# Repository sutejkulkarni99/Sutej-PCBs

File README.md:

# Sutej-PCBs
PCBs designs (Accenture Umlaut)

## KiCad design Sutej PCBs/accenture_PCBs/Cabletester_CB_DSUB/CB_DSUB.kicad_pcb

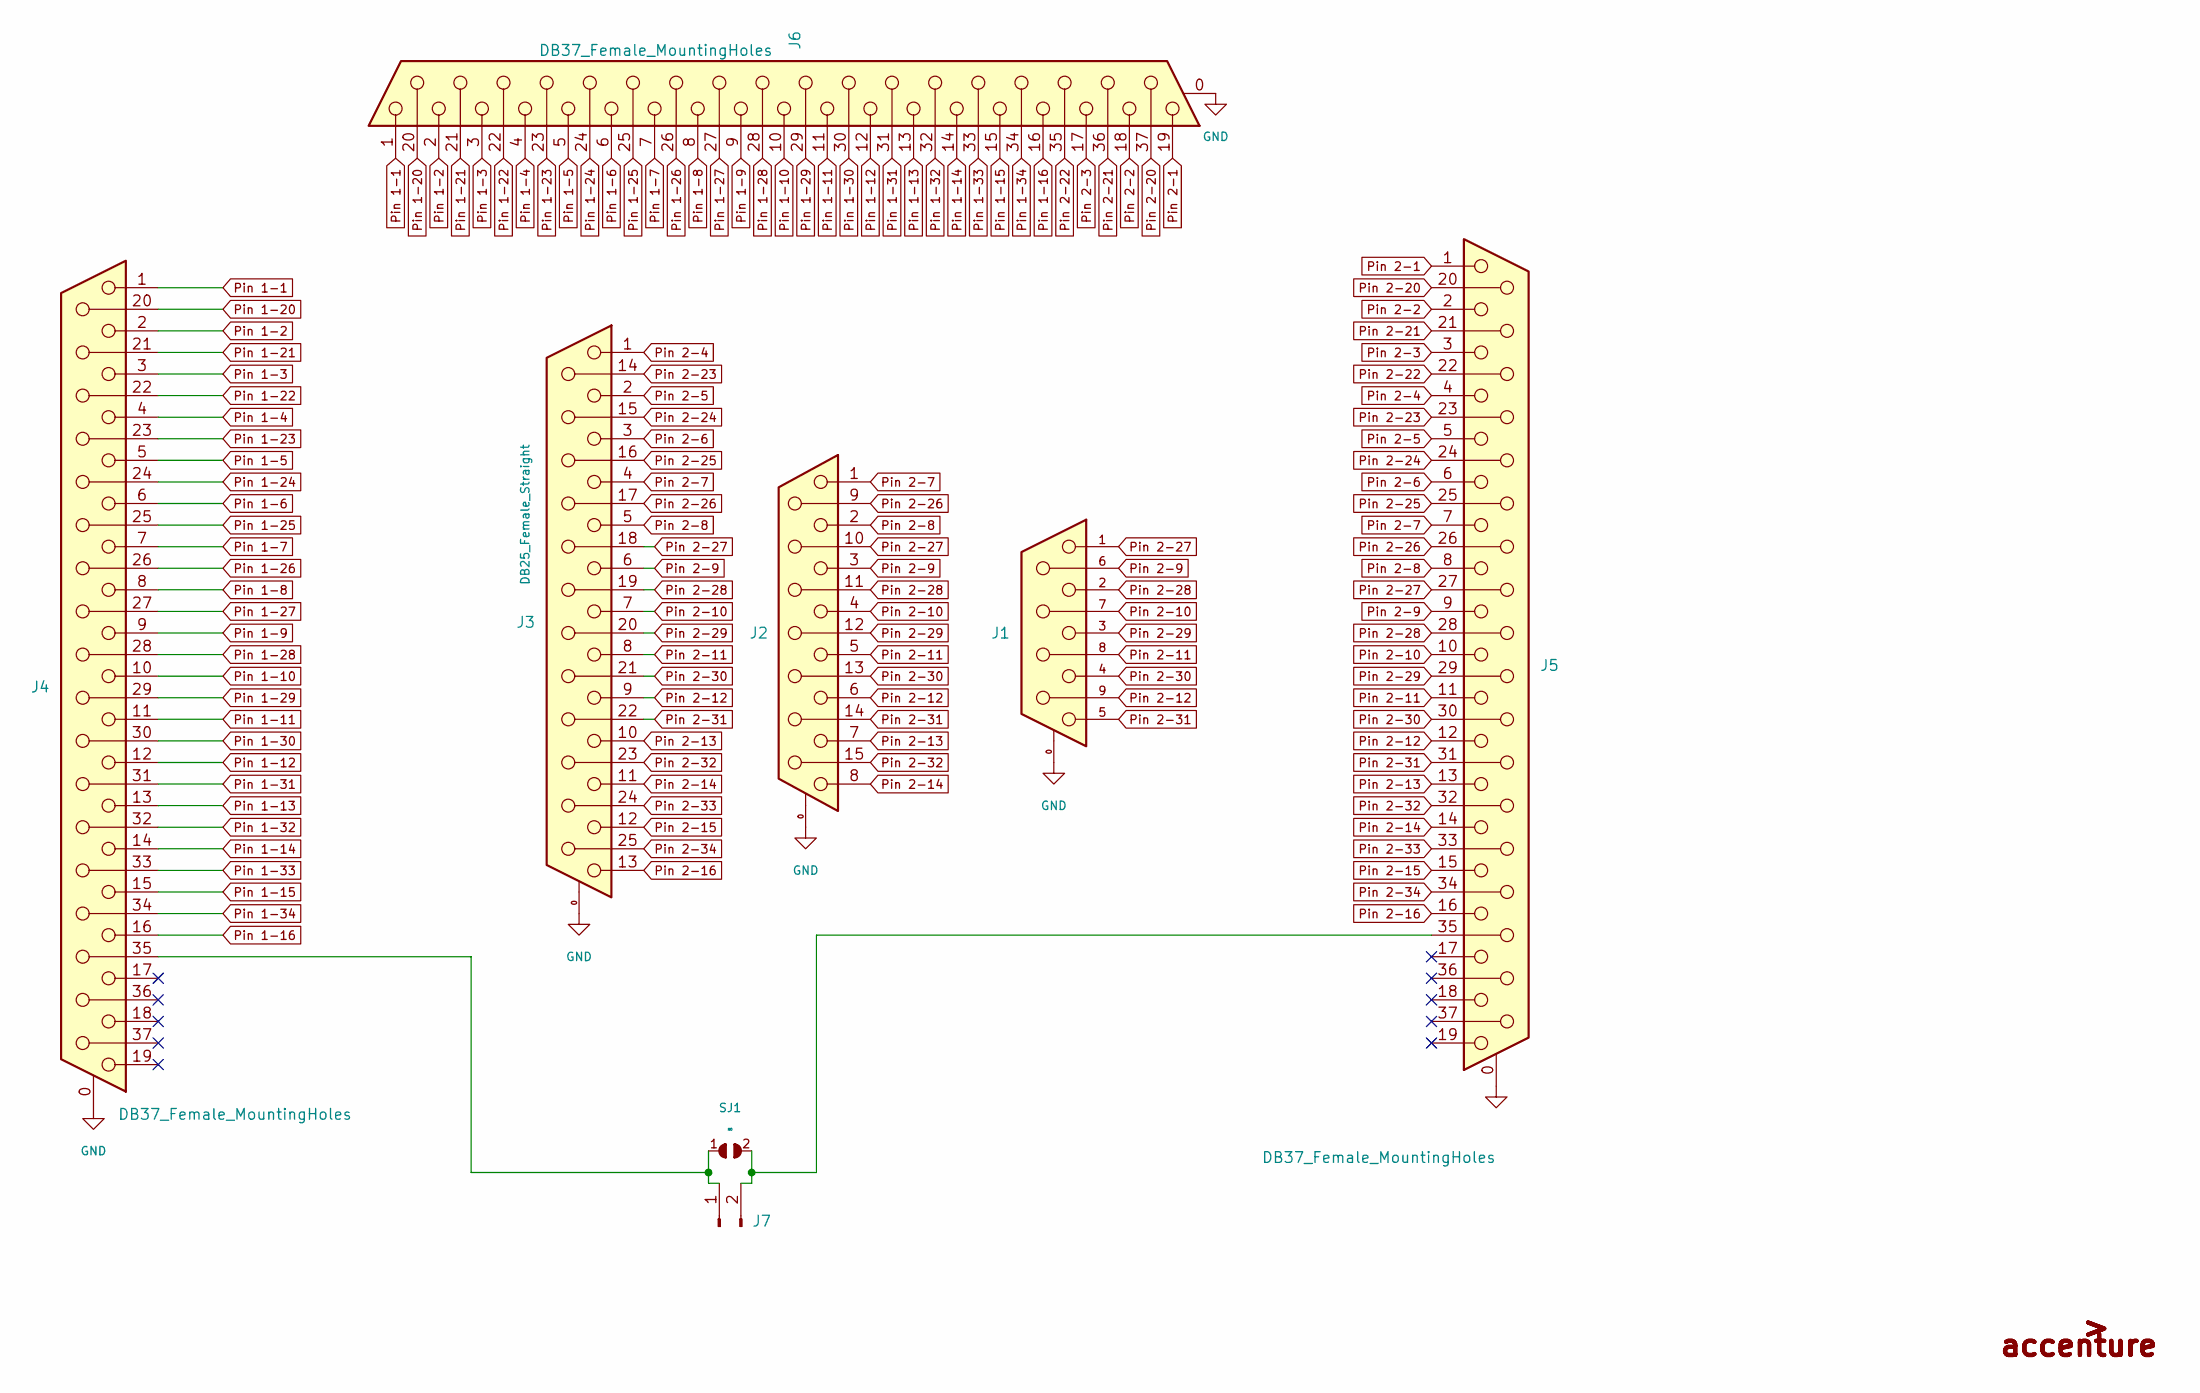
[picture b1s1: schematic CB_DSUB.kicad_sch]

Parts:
J1: DB9_Female_Straight; DSUB-9_Female_Vertical_P2.77x2.84mm_MountingHoles_FCC; Farnell 2401252
J2: DB15_Female_Straight; DSUB-15_Female_Vertical_P2.77x2.84mm_MountingHoles; Farnell 2857978
J3: DB25_Female_Straight; DSUB-25_Female_Vertical_P2.77x2.84mm-FCC; Farnell 3727279
J4, J5, J6: DB37_Female_MountingHoles; DSUB-37_Female_Vertical_P2.77x2.84mm_MountingHoles; Farnell 2401248
J7: Conn_01x02_Male; Molex_KK254_22032021_01_02x2.54mm_Straight; Farnell 9731075
Logo2, Logo3: Accenture-LOGO-13x3; Accenture-13x3
SJ1: SolderJumper-2pin; SJ

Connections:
GND: J1.0 (Shield), J2.0 (Shield), J3.0 (Shield), J4.0 (PAD), J5.0 (PAD), J6.0 (PAD)
unnamed: J4.35, J7.1, SJ1.1
unnamed: J5.35, J7.2, SJ1.2
Pin 1-1: J4.1, J6.1
Pin 1-2: J4.2, J6.2
Pin 1-3: J4.3, J6.3
Pin 1-4: J4.4, J6.4
Pin 1-5: J4.5, J6.5
Pin 1-6: J4.6, J6.6
Pin 1-7: J4.7, J6.7
Pin 1-8: J4.8, J6.8
Pin 1-9: J4.9, J6.9
Pin 1-10: J4.10, J6.10
Pin 1-11: J4.11, J6.11
Pin 1-12: J4.12, J6.12
Pin 1-13: J4.13, J6.13
Pin 1-14: J4.14, J6.14
Pin 1-15: J4.15, J6.15
Pin 1-16: J4.16, J6.16
Pin 1-20: J4.20, J6.20
Pin 1-21: J4.21, J6.21
Pin 1-22: J4.22, J6.22
Pin 1-23: J4.23, J6.23
Pin 1-24: J4.24, J6.24
Pin 1-25: J4.25, J6.25
Pin 1-26: J4.26, J6.26
Pin 1-27: J4.27, J6.27
Pin 1-28: J4.28, J6.28
Pin 1-29: J4.29, J6.29
Pin 1-30: J4.30, J6.30
Pin 1-31: J4.31, J6.31
Pin 1-32: J4.32, J6.32
Pin 1-33: J4.33, J6.33
Pin 1-34: J4.34, J6.34
Pin 2-1: J5.1, J6.19
Pin 2-2: J5.2, J6.18
Pin 2-3: J5.3, J6.17
Pin 2-4: J3.1, J5.4
Pin 2-5: J3.2, J5.5
Pin 2-6: J3.3, J5.6
Pin 2-7: J2.1, J3.4, J5.7
Pin 2-8: J2.2, J3.5, J5.8
Pin 2-9: J1.6, J2.3, J3.6, J5.9
Pin 2-10: J1.7, J2.4, J3.7, J5.10
Pin 2-11: J1.8, J2.5, J3.8, J5.11
Pin 2-12: J1.9, J2.6, J3.9, J5.12
Pin 2-13: J2.7, J3.10, J5.13
Pin 2-14: J2.8, J3.11, J5.14
Pin 2-15: J3.12, J5.15
Pin 2-16: J3.13, J5.16
Pin 2-20: J5.20, J6.37
Pin 2-21: J5.21, J6.36
Pin 2-22: J5.22, J6.35
Pin 2-23: J3.14, J5.23
Pin 2-24: J3.15, J5.24
Pin 2-25: J3.16, J5.25
Pin 2-26: J2.9, J3.17, J5.26
Pin 2-27: J1.1, J2.10, J3.18, J5.27
Pin 2-28: J1.2, J2.11 (P111), J3.19, J5.28
Pin 2-29: J1.3, J2.12, J3.20, J5.29
Pin 2-30: J1.4, J2.13, J3.21, J5.30
Pin 2-31: J1.5, J2.14, J3.22, J5.31
Pin 2-32: J2.15, J3.23, J5.32
Pin 2-33: J3.24, J5.33
Pin 2-34: J3.25, J5.34

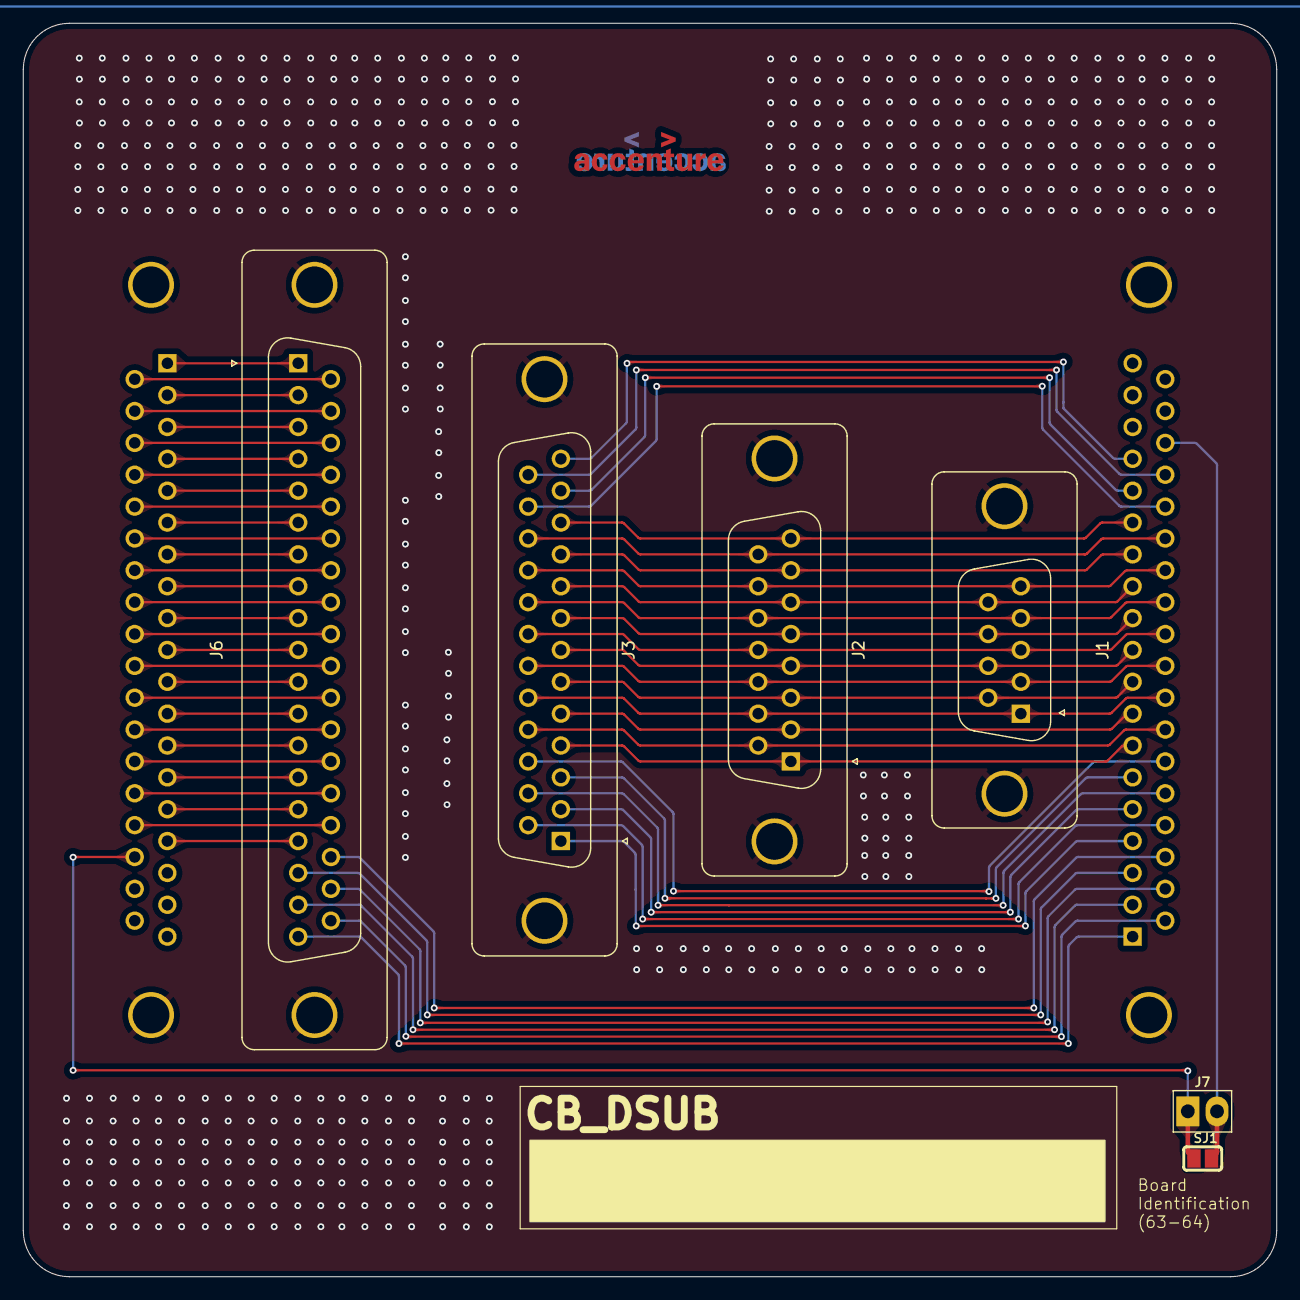
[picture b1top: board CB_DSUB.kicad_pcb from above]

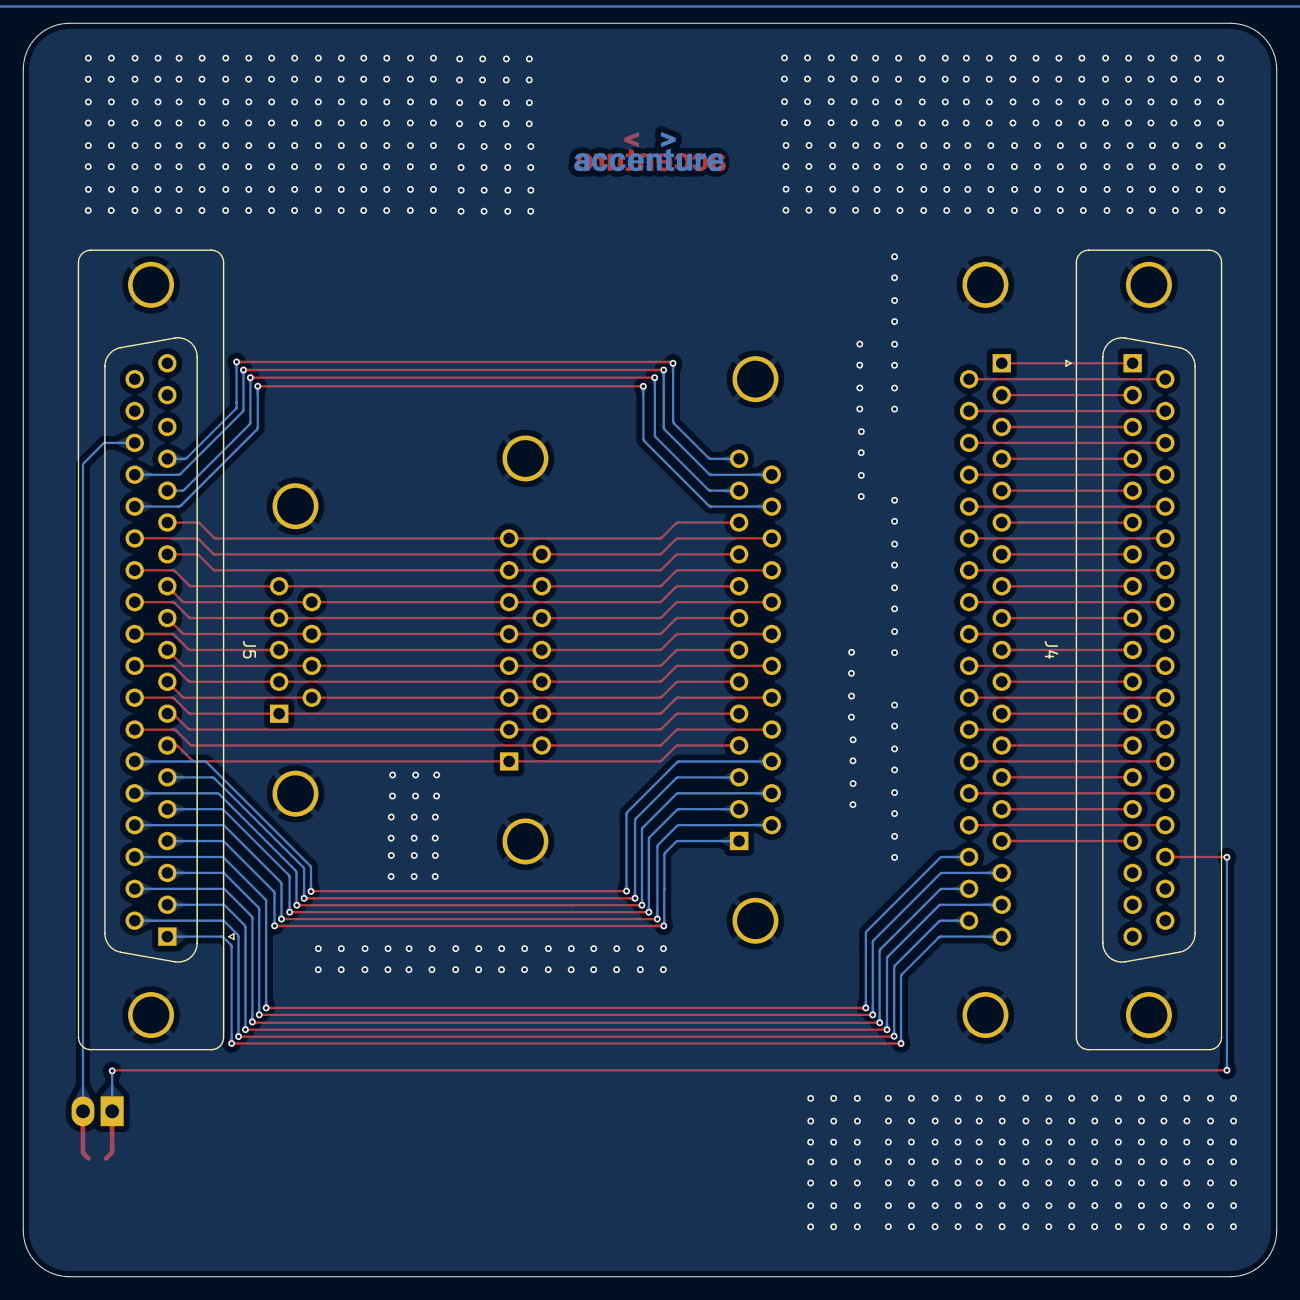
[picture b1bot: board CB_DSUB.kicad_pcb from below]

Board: 2 copper layers, 109.0 x 109.0 mm, 10 parts (3 on the bottom side), 65 nets.

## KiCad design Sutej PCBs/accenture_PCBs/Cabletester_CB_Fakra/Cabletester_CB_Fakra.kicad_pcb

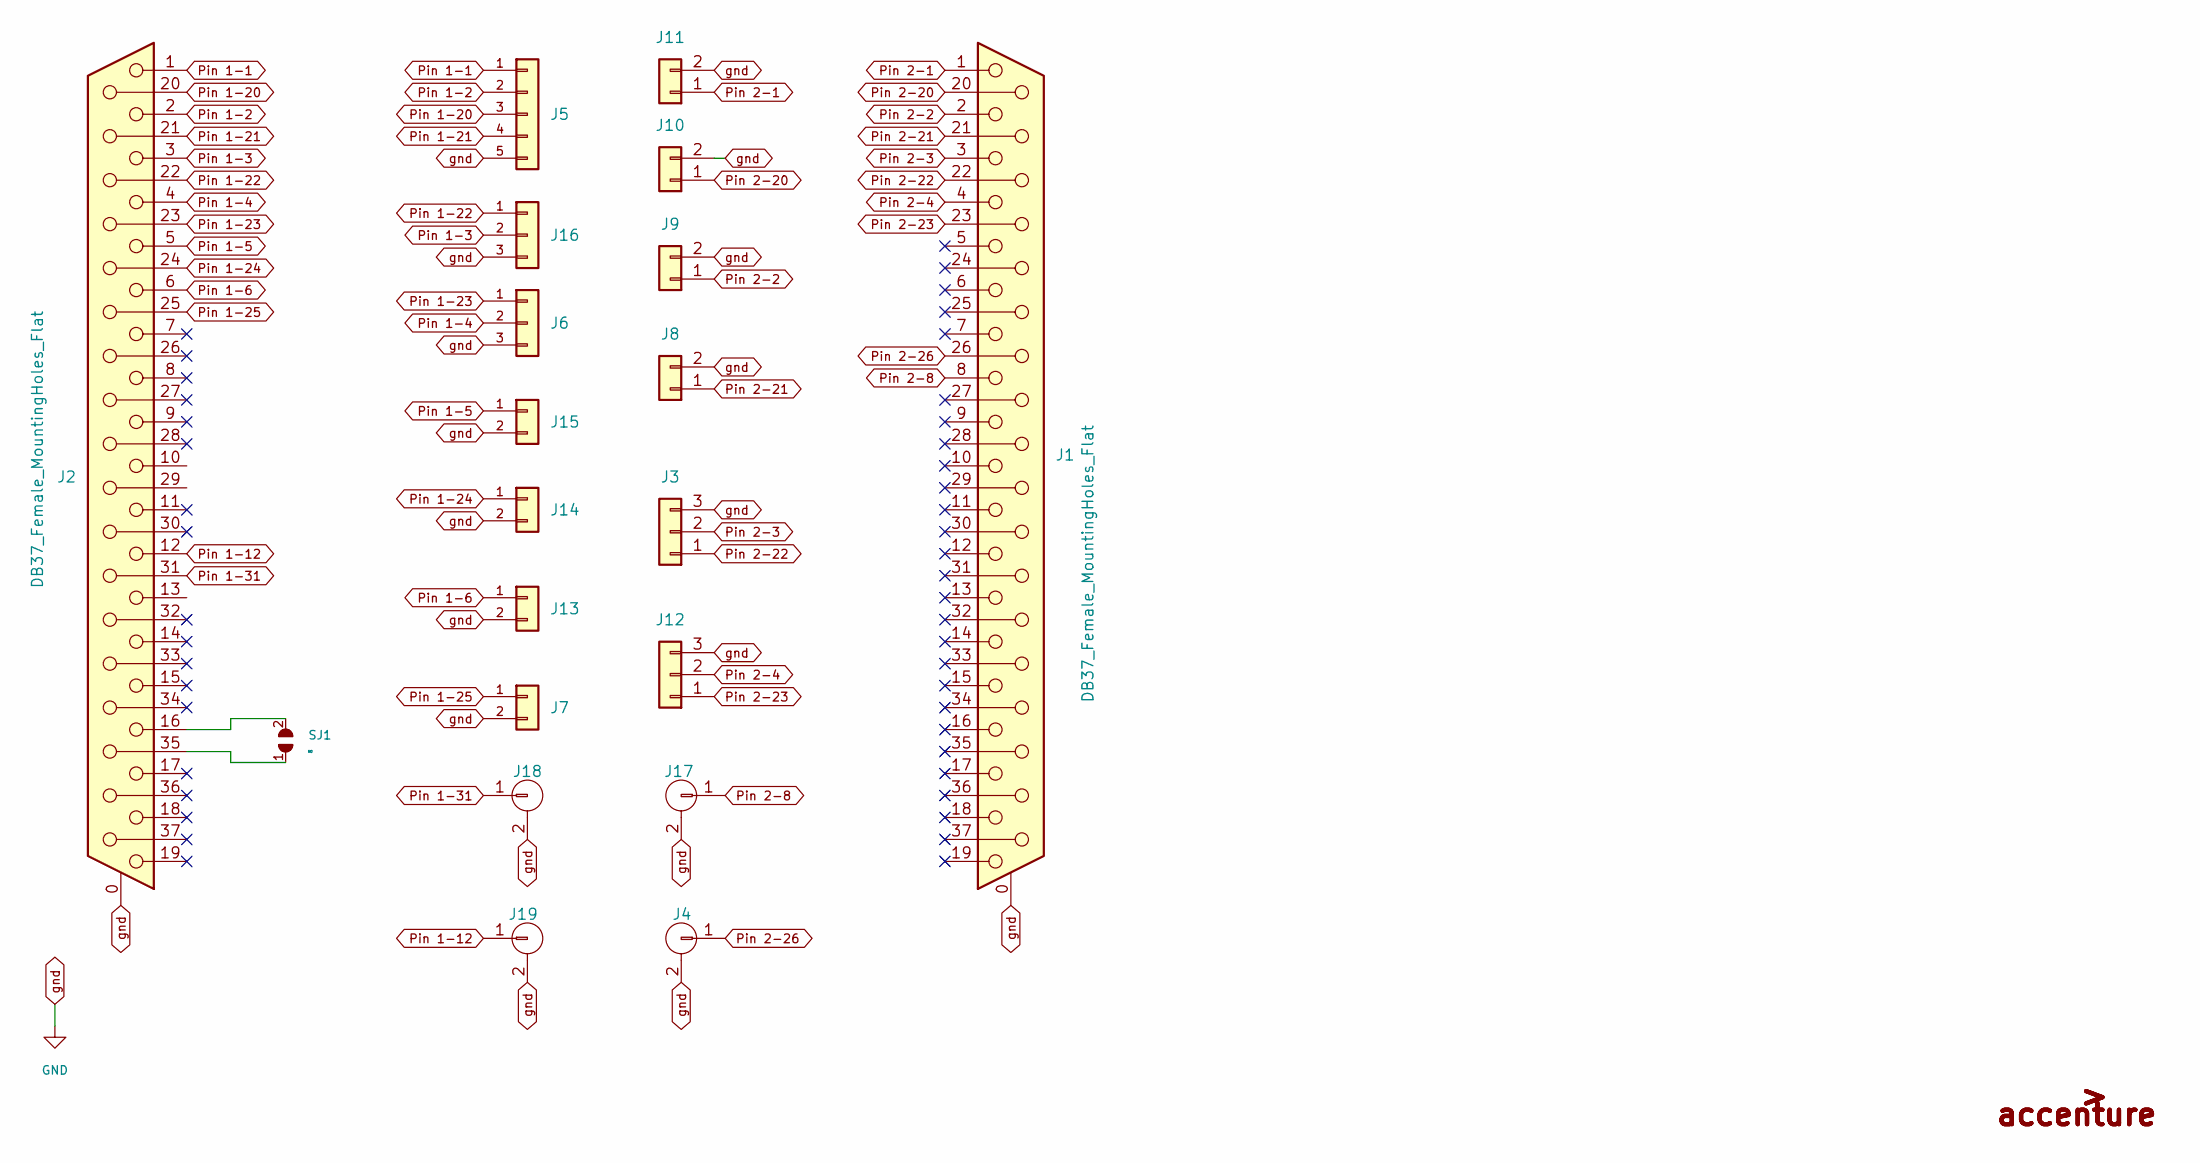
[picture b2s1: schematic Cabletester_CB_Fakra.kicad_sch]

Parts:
J1, J2: DB37_Female_MountingHoles_Flat; DSUB-37_Female_Vertical_P2.77x2.84mm_Flat_MountingHoles; Farnell 3882315
J3, J12: Rosenberger-59S2AA-400A5-G; 59S2AA-400A5-G
J4, J17, J18, J19: BNC-Female-PCB; BNC_731711900; Farnell 1909223
J5: Rosenberger-AMS29D-40MZ5-A; AMS29D-40MZ5-A
J6, J16: Rosenberger-AMS29B-40MZ5-Z; AMS29B-40MZ5-Z
J7, J13, J14, J15: Rosenberger-AMS29A-40MZ5-Z; AMS29A-40MZ5-Z
J8, J9, J10, J11: Rosenberger-59S2AQ-40MT5-C_1; 59S2AQ-40MT5-C_1
Logo1, Logo2: Accenture-LOGO-13x3; Accenture-13x3
SJ1: SolderJumper-2pin; SJ

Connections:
unnamed: J2.16, SJ1.2
unnamed: J2.35, SJ1.1
Pin 1-1: J2.1, J5.1
Pin 1-2: J2.2, J5.2
Pin 1-3: J2.3, J16.2
Pin 1-4: J2.4, J6.2
Pin 1-5: J2.5, J15.1
Pin 1-6: J2.6, J13.1
Pin 1-12: J2.12, J19.1
Pin 1-20: J2.20, J5.3 (Pin_2)
Pin 1-21: J2.21, J5.4 (Pin_2)
Pin 1-22: J2.22, J16.1
Pin 1-23: J2.23, J6.1
Pin 1-24: J2.24, J14.1
Pin 1-25: J2.25, J7.1
Pin 1-31: J2.31, J18.1
Pin 2-1: J1.1, J11.1
Pin 2-2: J1.2, J9.1
Pin 2-3: J1.3, J3.2
Pin 2-4: J1.4, J12.2
Pin 2-8: J1.8, J17.1
Pin 2-20: J1.20, J10.1
Pin 2-21: J1.21, J8.1
Pin 2-22: J1.22, J3.1
Pin 2-23: J1.23, J12.1
Pin 2-26: J1.26, J4.1
gnd: J1.0 (PAD), J2.0 (PAD), J3.3 (Pin_2), J4.2 (GND), J5.5 (Pin_2), J6.3 (Pin_2), J7.2, J8.2, J9.2, J10.2, J11.2, J12.3 (Pin_2), J13.2, J14.2, J15.2, J16.3 (Pin_2), J17.2 (GND), J18.2 (GND), J19.2 (GND)

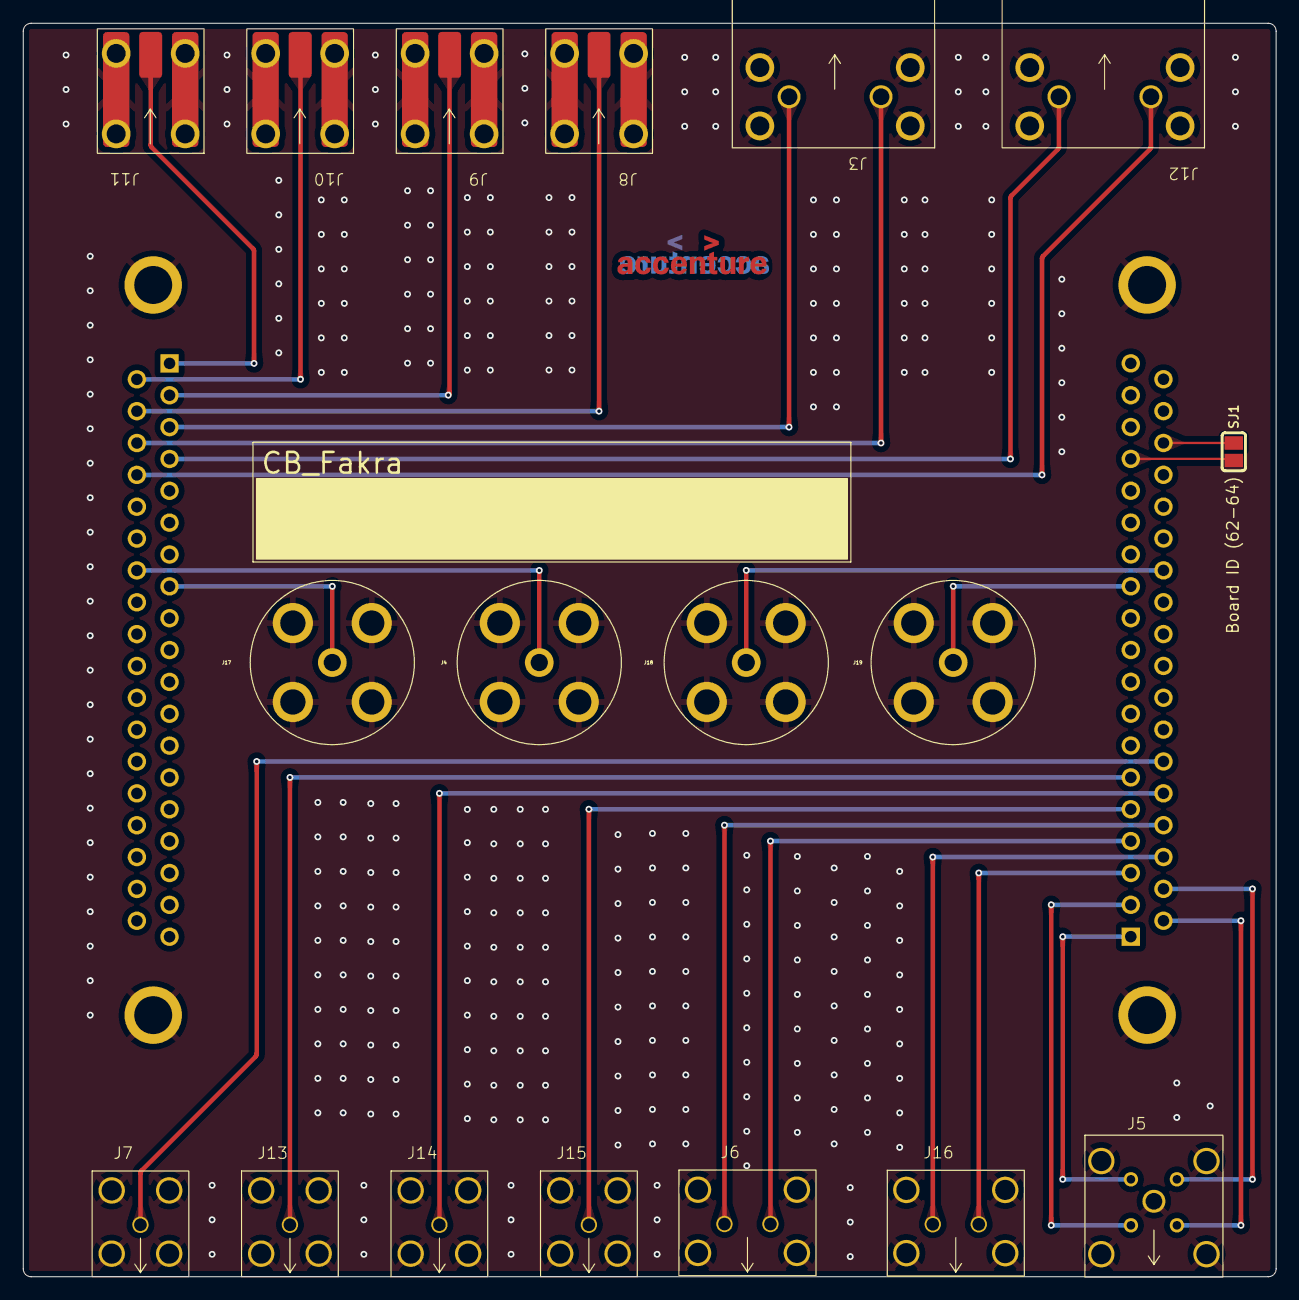
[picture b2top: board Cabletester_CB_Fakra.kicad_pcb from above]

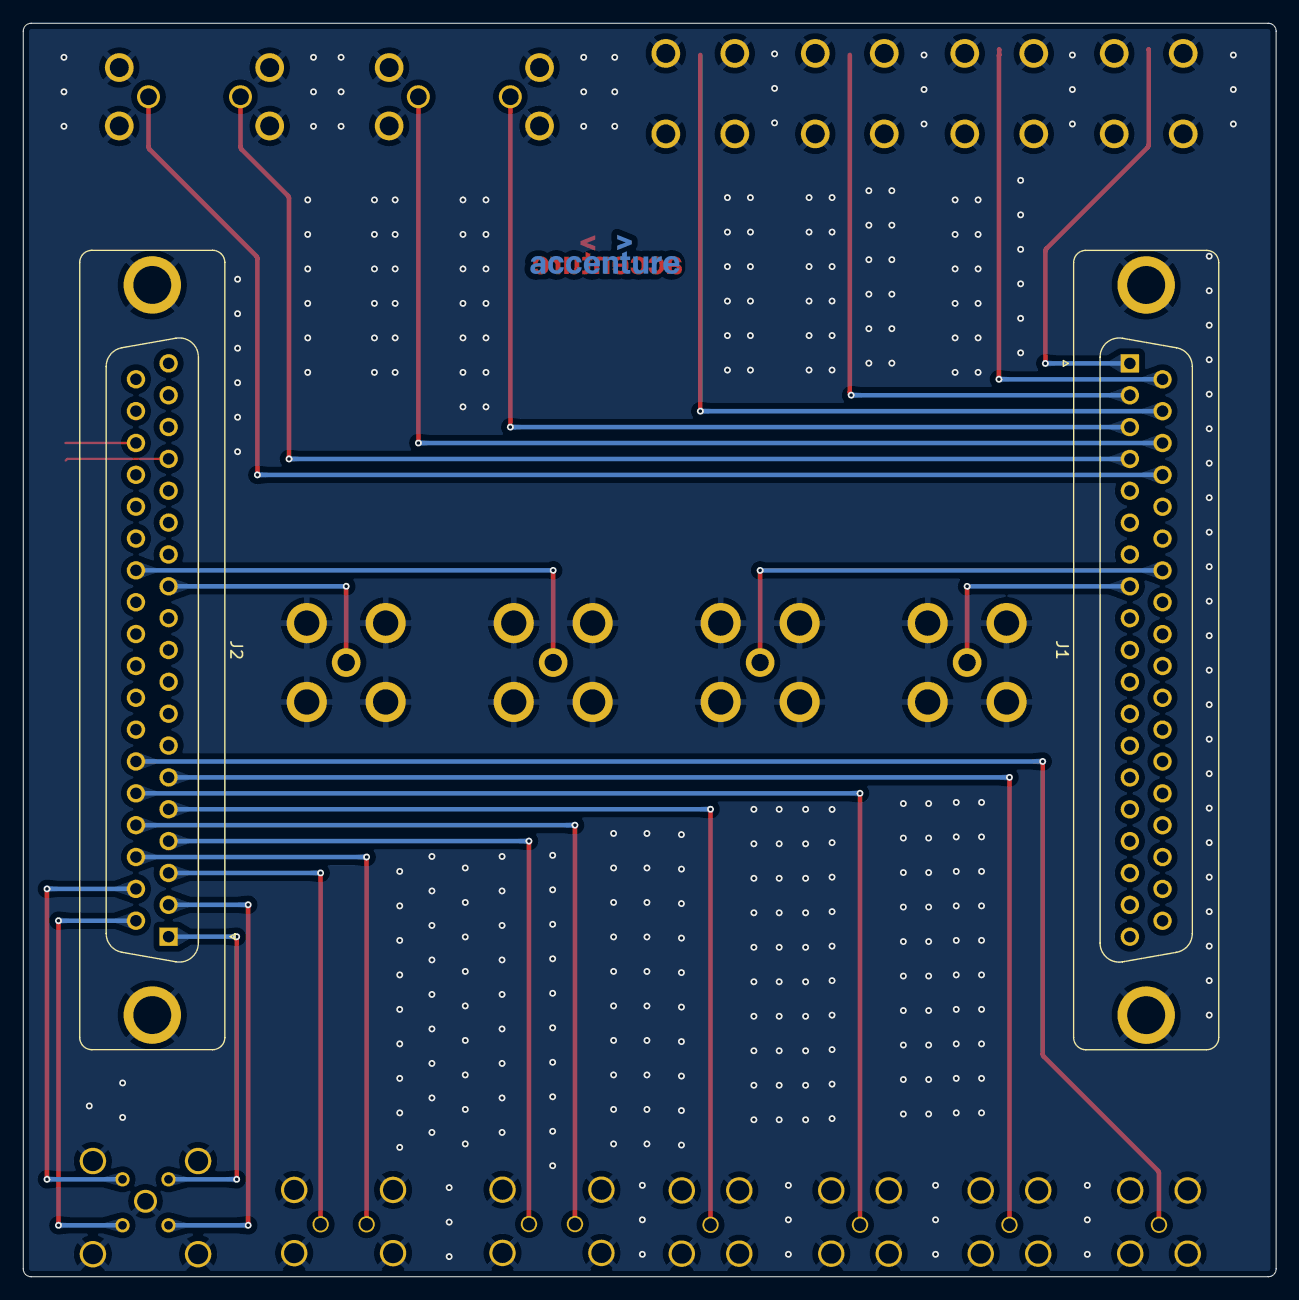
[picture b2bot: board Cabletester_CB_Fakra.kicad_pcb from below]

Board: 2 copper layers, 109.0 x 109.0 mm, 22 parts (3 on the bottom side), 27 nets.

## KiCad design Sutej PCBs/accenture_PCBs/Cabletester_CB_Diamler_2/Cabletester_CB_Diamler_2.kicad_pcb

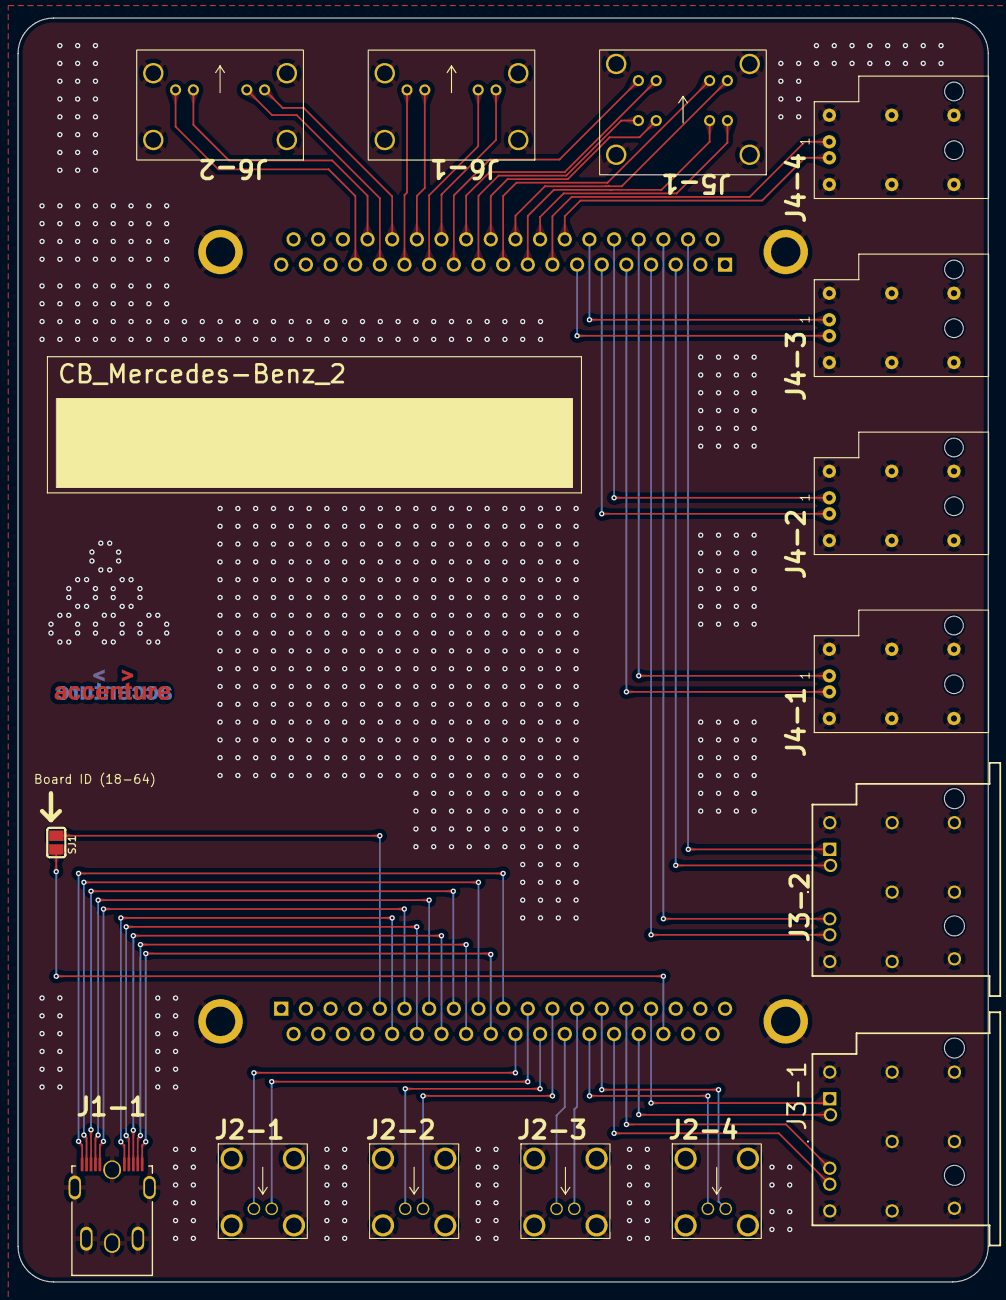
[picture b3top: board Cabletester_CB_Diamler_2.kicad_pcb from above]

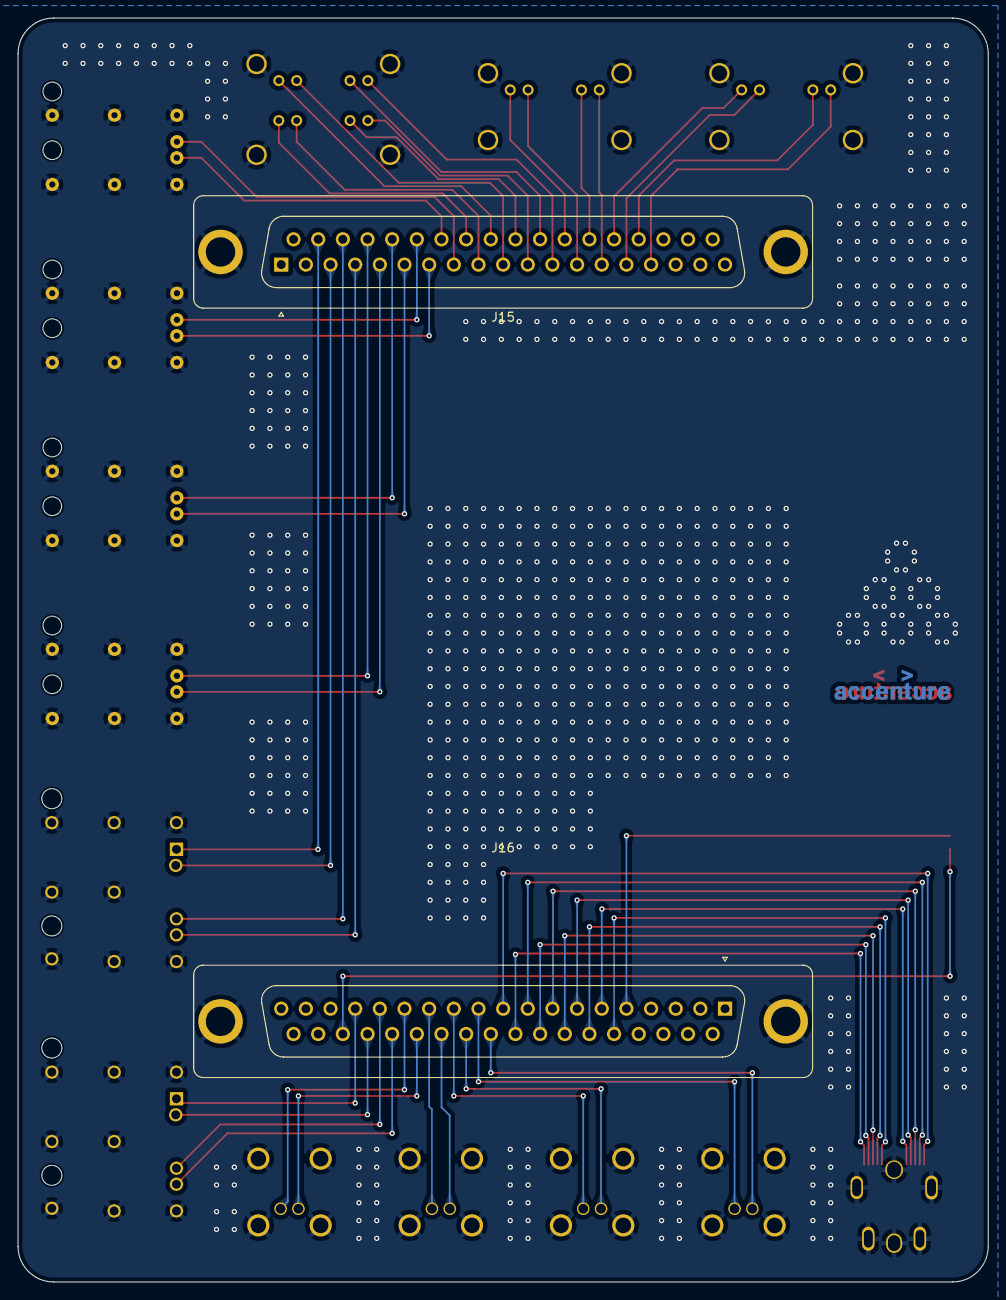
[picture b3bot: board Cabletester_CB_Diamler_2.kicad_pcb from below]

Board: 2 copper layers, 109.0 x 142.0 mm, 19 parts (3 on the bottom side), 53 nets.

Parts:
J1-1: Daimler-IX61G-A-10P; IX61G-A-10P
J2-1, J2-2, J2-3, J2-4: Rosenberger-E6S20A-40MT5-Z; E6S20A-40MT5-Z
J3-1, J3-2: TE-9-2305987-9; 9-2305987-9
J4-1, J4-2, J4-3, J4-4: Conn_01x04_1.27mm_Female; TE-c-9-2304372-9-a
J5-1: Rosenberger-E6S20D-40MT5-Z; E6S20D-40MT5-Z
J6-1, J6-2: Rosenberger-E6S20B-40MT5-Z; E6S20B-40MT5-Z
J15, J16: DB37_Female_MountingHoles_Flat; DSUB-37_Female_Vertical_P2.77x2.84mm_Flat_MountingHoles
Logo1, Logo2: Accenture-LOGO-13x3; Accenture-13x3
SJ1: SolderJumper-2pin; SJ

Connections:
GND: J1-1.11 (GND), J2-1.3 (Pin_2), J2-2.3 (Pin_2), J2-3.3 (Pin_2), J2-4.3 (Pin_2), J3-1.5, J3-2.5, J4-1.3, J4-1.4, J4-2.3, J4-2.4, J4-3.3, J4-3.4, J4-4.3, J4-4.4, J5-1.5 (Pin_2), J6-1.5 (Pin_2), J6-2.5 (Pin_2), J15.0 (PAD), J16.0 (PAD)
unnamed: J16.5, SJ1.1
unnamed: J16.35, SJ1.2
Pin 1-3: J3-2.2, J15.3
Pin 1-4: J3-2.4, J15.4
Pin 1-5: J4-1.2, J15.5
Pin 1-6: J4-2.2, J15.6
Pin 1-7: J4-3.2, J15.7
Pin 1-8: J4-4.1, J15.8
Pin 1-9: J5-1.1-2 (Pair1), J15.9
Pin 1-10: J5-1.4-1 (Pair4), J15.10
Pin 1-11: J5-1.2-2 (Pair2), J15.11
Pin 1-12: J5-1.3-1 (Pair3), J15.12
Pin 1-13: J6-1.2, J15.13
Pin 1-14: J6-1.4 (Pin_2), J15.14
Pin 1-15: J6-2.2, J15.15
Pin 1-16: J6-2.4 (Pin_2), J15.16
Pin 1-21: J3-2.1, J15.21
Pin 1-22: J3-2.3, J15.22
Pin 1-23: J4-1.1, J15.23
Pin 1-24: J4-2.1, J15.24
Pin 1-25: J4-3.1, J15.25
Pin 1-26: J4-4.2, J15.26
Pin 1-27: J5-1.1-1 (Pair1), J15.27
Pin 1-28: J5-1.4-2 (Pair4), J15.28
Pin 1-29: J5-1.2-1 (Pair2), J15.29
Pin 1-30: J5-1.3-2 (Pair3), J15.30
Pin 1-31: J6-1.1, J15.31
Pin 1-32: J6-1.3 (Pin_2), J15.32
Pin 1-33: J6-2.1, J15.33
Pin 1-34: J6-2.3 (Pin_2), J15.34
Pin 2-6: J1-1.5 (ICSP_CLK), J16.6
Pin 2-7: J1-1.4 (ICSP_DATA), J16.7
Pin 2-8: J1-1.3 (GND), J16.8
Pin 2-9: J1-1.2 (Vcc), J16.9
Pin 2-10: J1-1.1 (Reset), J16.10
Pin 2-11: J2-1.2, J16.11
Pin 2-12: J2-2.2, J16.12
Pin 2-13: J2-3.2, J16.13
Pin 2-14: J2-4.2, J16.14
Pin 2-15: J3-1.3, J16.15
Pin 2-16: J3-1.1, J16.16
Pin 2-24: J1-1.6, J16.24
Pin 2-25: J1-1.7, J16.25
Pin 2-26: J1-1.8, J16.26
Pin 2-27: J1-1.9, J16.27
Pin 2-28: J1-1.10, J16.28
Pin 2-29: J2-1.1, J16.29
Pin 2-30: J2-2.1, J16.30
Pin 2-31: J2-3.1, J16.31
Pin 2-32: J2-4.1, J16.32
Pin 2-33: J3-1.4, J16.33
Pin 2-34: J3-1.2, J16.34

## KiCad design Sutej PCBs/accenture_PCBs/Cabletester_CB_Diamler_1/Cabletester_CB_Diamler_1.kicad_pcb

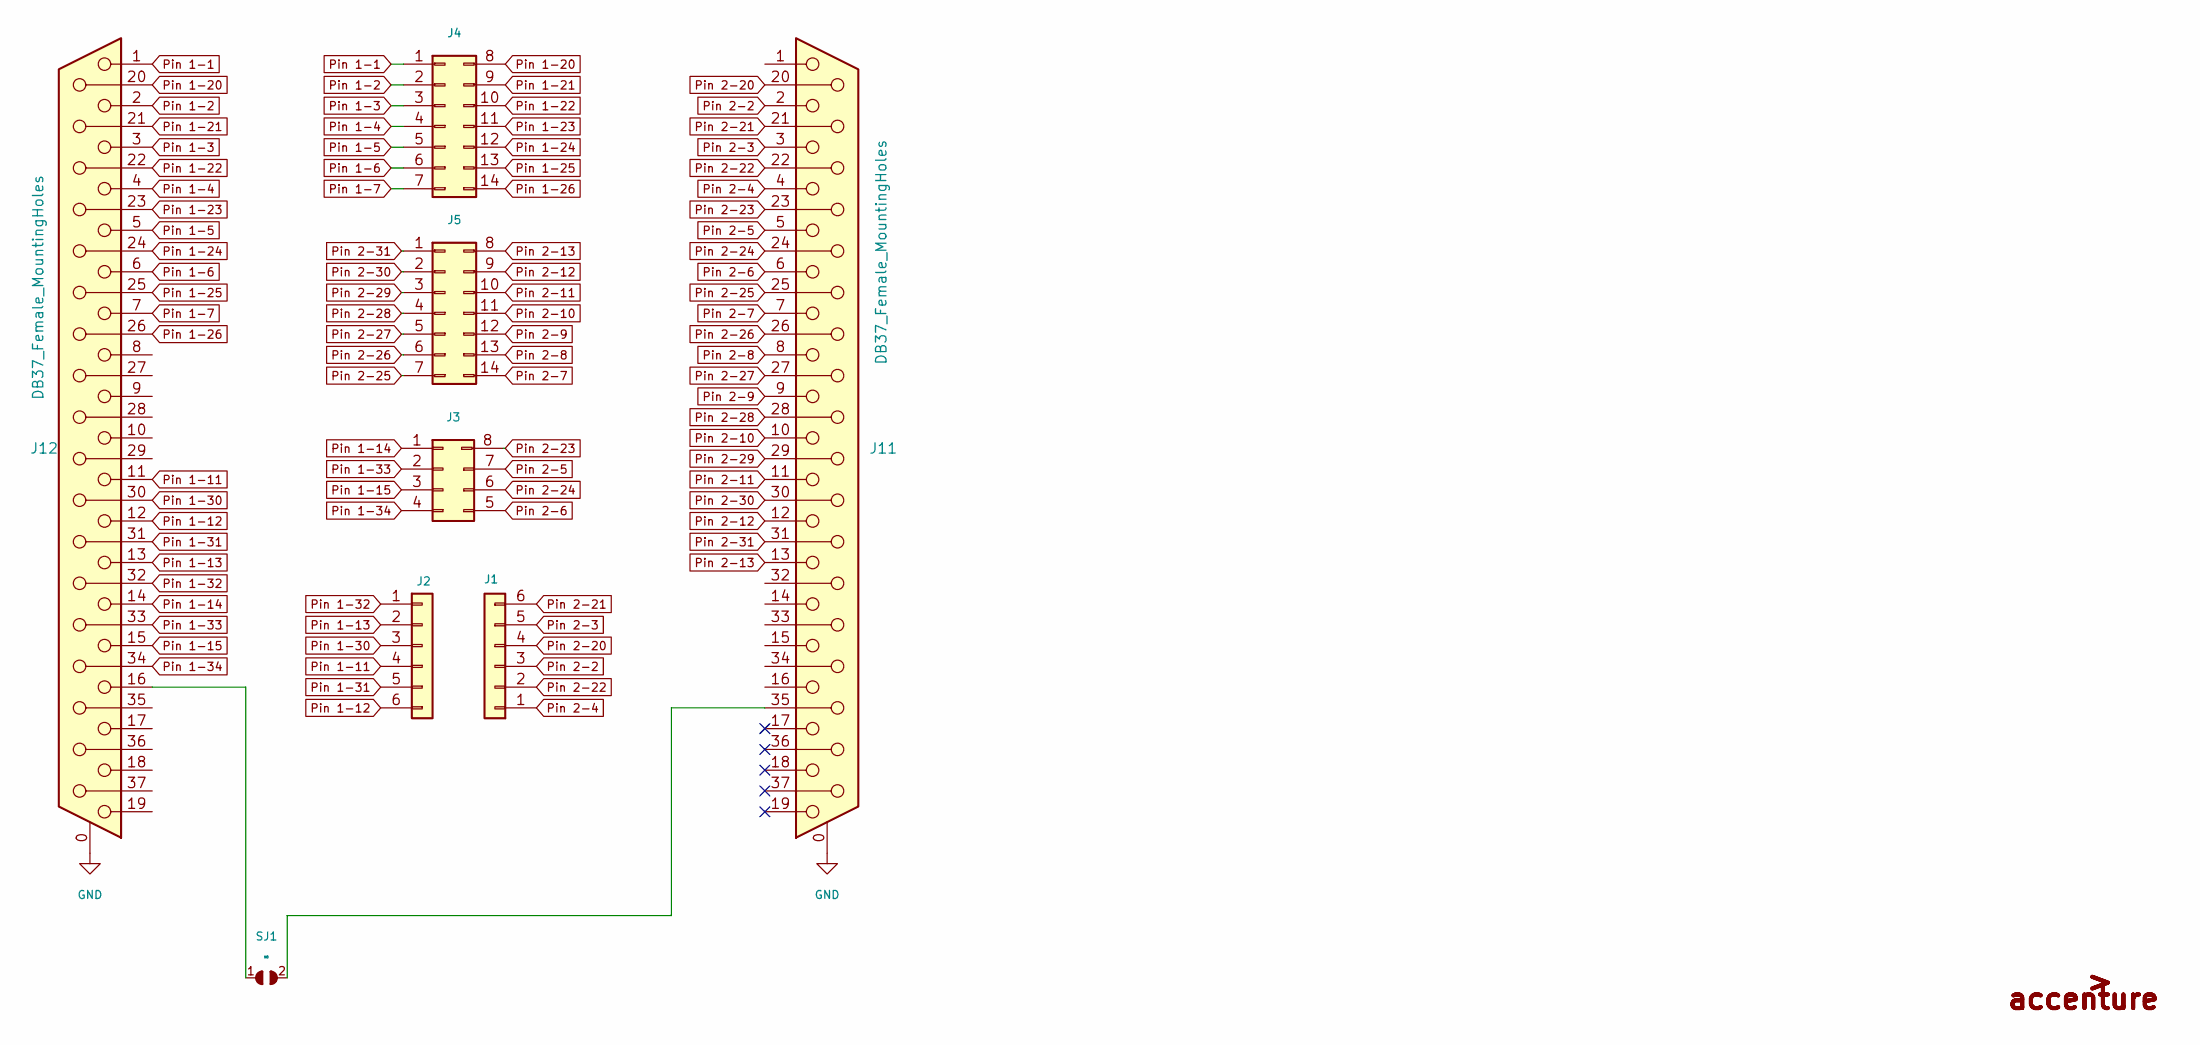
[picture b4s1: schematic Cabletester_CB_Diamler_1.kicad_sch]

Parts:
J1, J2: Daimler-MMBox-01x06; MM-Box
J3: Daimler-Display-02x4; Display2x4
J4: Daimler-MMBoxPigtail-White; MMBox-Pigtail-White
J5: Daimler-MMBoxPigtail-Blue; MMBox-Pigtail-Blue
J11, J12: DB37_Female_MountingHoles; DSUB-37_Female_Vertical_P2.77x2.84mm_MountingHoles; Farnell 2401248
Logo3, Logo4: Accenture-LOGO-13x3; Accenture-13x3
SJ1: SolderJumper-2pin; SJ

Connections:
GND: J11.0 (PAD), J12.0 (PAD)
unnamed: J11.35, SJ1.2
unnamed: J12.16, SJ1.1
Pin 1-1: J4.1 (Reset), J12.1
Pin 1-2: J4.2 (Vcc), J12.2
Pin 1-3: J4.3 (GND), J12.3
Pin 1-4: J4.4 (ICSP_DATA), J12.4
Pin 1-5: J4.5 (ICSP_CLK), J12.5
Pin 1-6: J4.6 (GND), J12.6
Pin 1-7: J4.7 (GND), J12.7
Pin 1-11: J2.4 (ICSP_DATA), J12.11
Pin 1-12: J2.6 (GND), J12.12
Pin 1-13: J2.2 (Vcc), J12.13
Pin 1-14: J3.1 (Reset), J12.14
Pin 1-15: J3.3 (GND), J12.15
Pin 1-20: J4.8 (Reset), J12.20
Pin 1-21: J4.9 (Vcc), J12.21
Pin 1-22: J4.10 (GND), J12.22
Pin 1-23: J4.11 (ICSP_DATA), J12.23
Pin 1-24: J4.12 (ICSP_CLK), J12.24
Pin 1-25: J4.13 (GND), J12.25
Pin 1-26: J4.14 (GND), J12.26
Pin 1-30: J2.3 (GND), J12.30
Pin 1-31: J2.5 (ICSP_CLK), J12.31
Pin 1-32: J2.1 (Reset), J12.32
Pin 1-33: J3.2 (Vcc), J12.33
Pin 1-34: J3.4 (ICSP_DATA), J12.34
Pin 2-2: J1.3 (GND), J11.2
Pin 2-3: J1.5 (ICSP_CLK), J11.3
Pin 2-4: J1.1 (Reset), J11.4
Pin 2-5: J3.7 (GND), J11.5
Pin 2-6: J3.5 (GND), J11.6
Pin 2-7: J5.14 (GND), J11.7
Pin 2-8: J5.13 (GND), J11.8
Pin 2-9: J5.12 (ICSP_CLK), J11.9
Pin 2-10: J5.11 (ICSP_DATA), J11.10
Pin 2-11: J5.10 (GND), J11.11
Pin 2-12: J5.9 (Vcc), J11.12
Pin 2-13: J5.8 (Reset), J11.13
Pin 2-20: J1.4 (ICSP_DATA), J11.20
Pin 2-21: J1.6 (GND), J11.21
Pin 2-22: J1.2 (Vcc), J11.22
Pin 2-23: J3.8 (GND), J11.23
Pin 2-24: J3.6 (GND), J11.24
Pin 2-25: J5.7 (GND), J11.25
Pin 2-26: J5.6 (GND), J11.26
Pin 2-27: J5.5 (ICSP_CLK), J11.27
Pin 2-28: J5.4 (ICSP_DATA), J11.28
Pin 2-29: J5.3 (GND), J11.29
Pin 2-30: J5.2 (Vcc), J11.30
Pin 2-31: J5.1 (Reset), J11.31
